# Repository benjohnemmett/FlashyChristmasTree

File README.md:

# Flashy Christmas Tree
This is a project created in KiCad 7 to be cut out from an adhesive copper sheet using a craft cutting machine.

More details can be found here https://benjemmett.com/archives/1035

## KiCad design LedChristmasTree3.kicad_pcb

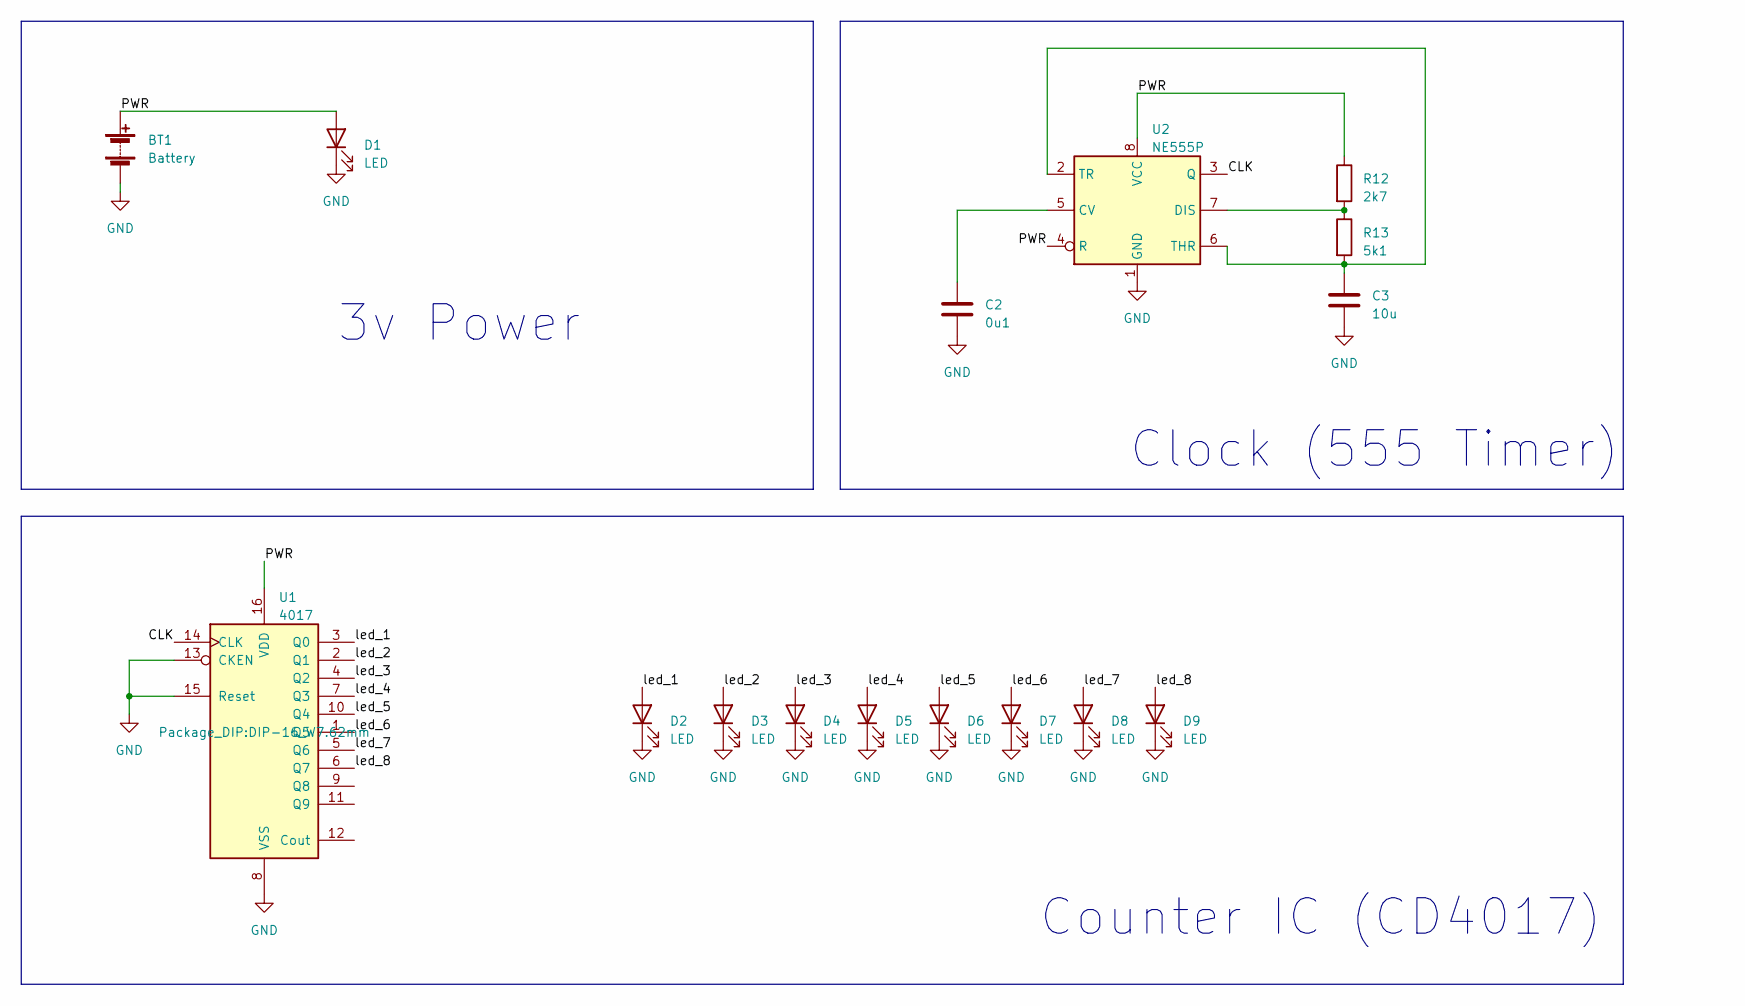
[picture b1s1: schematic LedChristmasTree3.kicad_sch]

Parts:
BT1: Battery; battery_holder_CR2032_vertical
C2: 0u1; C_0805_2012Metric_Pad1.18x1.45mm_HandSolder
C3: 10u; C_0805_2012Metric_Pad1.18x1.45mm_HandSolder
D1, D2, D3, D4, D5, D6, D7, D8, D9: LED; LED_D3.0mm
R12: 2k7; R_0805_2012Metric_Pad1.20x1.40mm_HandSolder
R13: 5k1; R_0805_2012Metric_Pad1.20x1.40mm_HandSolder
U1: 4017; DIP-16_W7.62mm
U2: NE555P; DIP-8_W7.62mm

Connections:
/CLK: U1.14 (CLK), U2.3 (Q)
/PWR: BT1.1 (+), D1.2 (A), R12.1, U1.16 (VDD), U2.4 (R), U2.8 (VCC)
/THRESHOLD: C3.1, R13.2, U2.2 (TR), U2.6 (THR)
/led_1: D2.2 (A), U1.3 (Q0)
/led_2: D3.2 (A), U1.2 (Q1)
/led_3: D4.2 (A), U1.4 (Q2)
/led_4: D5.2 (A), U1.7 (Q3)
/led_5: D6.2 (A), U1.10 (Q4)
/led_6: D7.2 (A), U1.1 (Q5)
/led_7: D8.2 (A), U1.5 (Q6)
/led_8: D9.2 (A), U1.6 (Q7)
GND: BT1.2 (-), C2.2, C3.2, D1.1 (K), D2.1 (K), D3.1 (K), D4.1 (K), D5.1 (K), D6.1 (K), D7.1 (K), D8.1 (K), D9.1 (K), U1.8 (VSS), U1.13 (CKEN), U1.15 (Reset), U2.1 (GND)
unnamed: C2.1, U2.5 (CV)
unnamed: R12.2, R13.1, U2.7 (DIS)

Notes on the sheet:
3v Power
Counter IC (CD4017)
Clock (555 Timer)

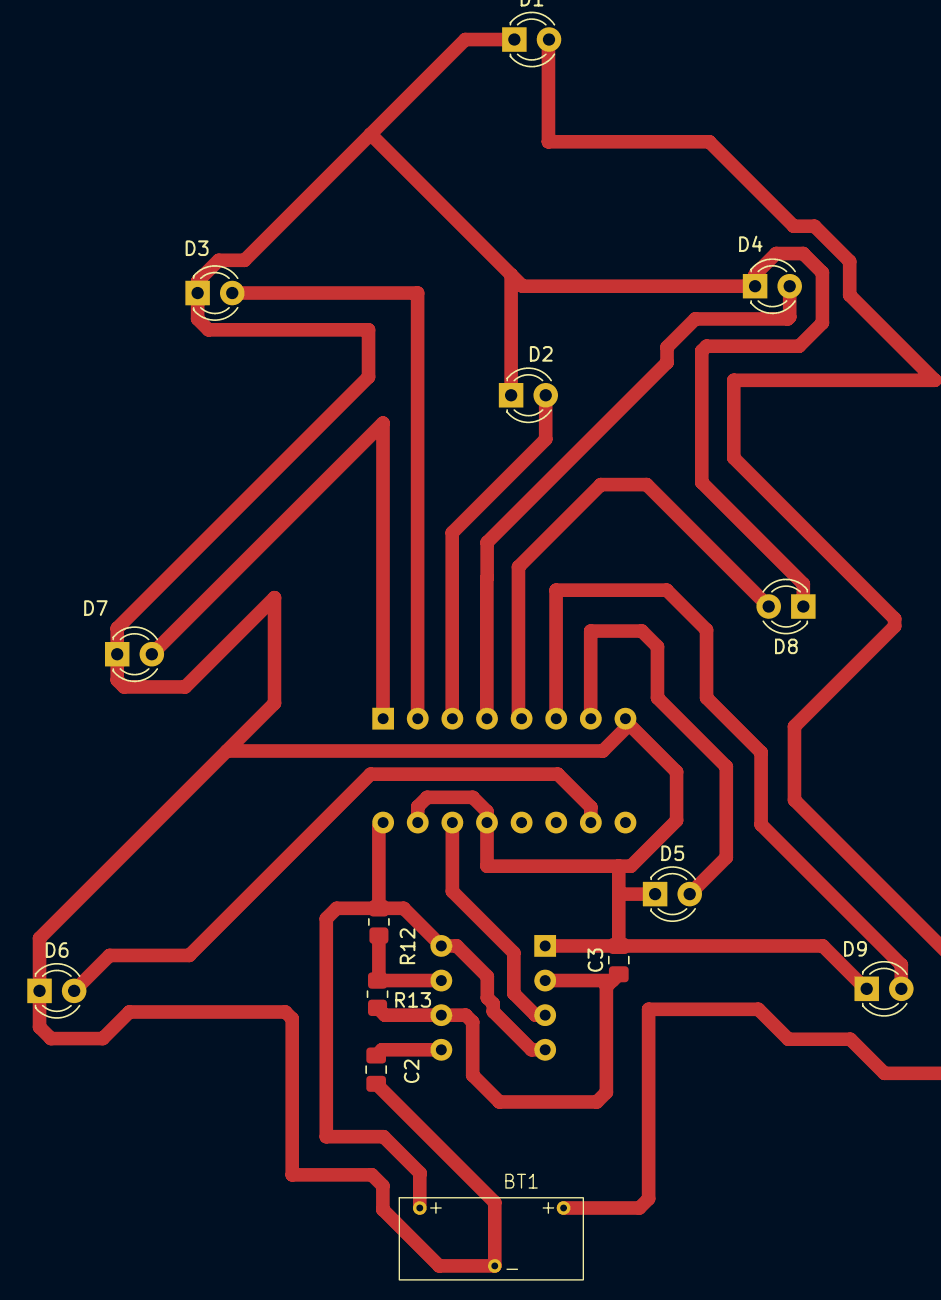
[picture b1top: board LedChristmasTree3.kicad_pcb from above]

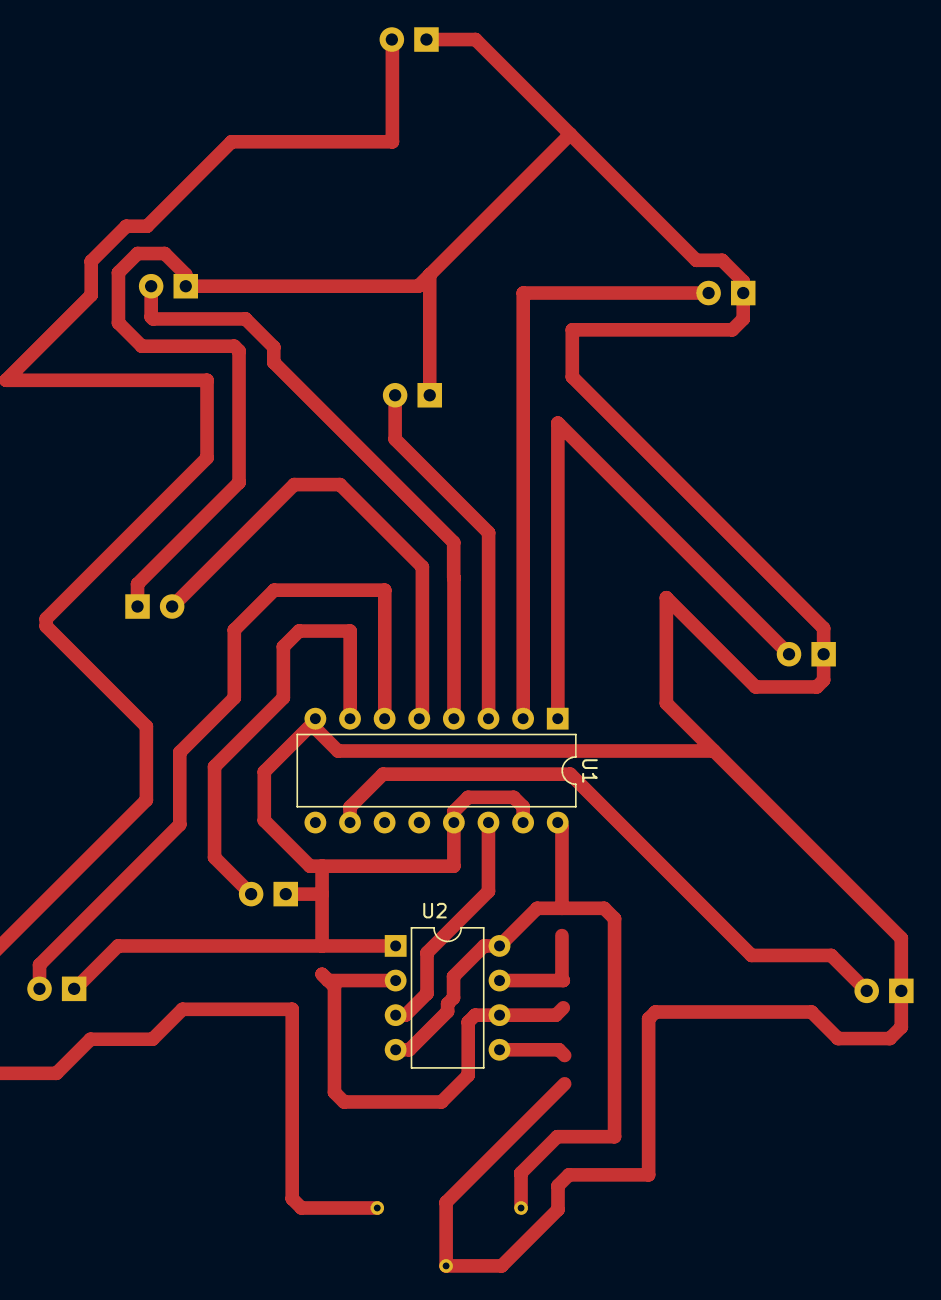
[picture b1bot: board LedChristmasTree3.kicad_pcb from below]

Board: 2 copper layers, 16 parts (2 on the bottom side), 14 nets.

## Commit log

2024-12-08 Adding silhouette studio & image files.
